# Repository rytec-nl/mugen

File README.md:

# Mugen, my implementation

This project is born because I wanted to connect an external amplifier to my Samsung smart tv that fits my tv cabinet.
The obvious step was to build a hybrid tube/transistor amplifier myself. I was pointed to the Mugen hybrid amplifier. It fit my size and power requirements (I have 2 60W Visaton speakers). Altough there were some things that need to be added for it to work with my setup. 

For one i want to use my tv remote to change the volume, so I will need to implement a IR reciever that controls a variable resistor in the input signal. This means an additional power supply, a microcontroller to process the IR signals and control a digital potentiometer. 

The next challenge is that my TV only has an optical audio out, so I need to hook up a optical to aux convertor. My plan as of now is to buy the smallest I can find and build it into the amplifier. If this proves impossible, it will stay as an external box. 

Finally I want the amplifier to look good. So I am planning to change the design to have both tubes above eachother when facing the front of the amplifier. I can then place a see through window in front of the Tubes so they can be seen. Then hookup some LEDs to the microcontroller, and place them behind the tubes for some cool effects. Using the Microcontroller I can the dim the LEDs using a PWM signal. This all being carefull not to let the PWM signal interfere with the audio signal.

## Additions

As I'm working on the amplifier the design is improving. Instead of using plain windows in front of the tubes, the idea now is to use LCD displays where the backlight is removed. This gives a transparent view inside the amplifier when nothing is displayed. When needed lights inside the amp. will light up, and whatever is shown on the LCD becomes visible. This will be used for volume indication. 

In order for this to be implemented, in stead of simply adding a power supply to the main power board, a completely extra PCB will be added for the logic needed. 

## Todo

- [ ] Power Supply
   - [x] original schematic
   - [ ] schematic review 
   - [x] PCB
   - [ ] PCB review 
- [ ] Amplifier
   - [x] schematic 
   - [ ] schematic review
   - [ ] PCB
   - [ ] PCB review
- [ ] Logic board
   - [ ] schematic 
   - [ ] schematic review
   - [ ] PCB
   - [ ] PCB review
- [ ] Case
   - [ ] Front
      - [ ] design
      - [ ] build
   - [ ] back
      - [ ] design
      - [ ] build
   - [ ] bottom/top
   - [ ] sides
 - [ ] Firmware
    - [x] IR reciever test
    - [ ] IR reciever
    - [ ] Volume control
    - [ ] LED PWM
    - [ ] LED Level Control
    - [x] LCD control test
    - [ ] LCD control

## KiCad

The PCBs are designed using [KiCad](http://kicad.org/). This is the most usable free PCB design software I could find, that also works on Linux. Before this project I normally would use [Eagle](https://www.autodesk.com/products/eagle/overview), I even started this project using Eagle. But for me it is just to expensive for boards larger than `160mm x 100mm` ($65/month or in my case €85/month). So I chose a free alternative, that so far I am liking very much!

## Power Supply

### Schematic & PCB

### 3D View

## Amplifier

### Schematic & PCB

### 3D View

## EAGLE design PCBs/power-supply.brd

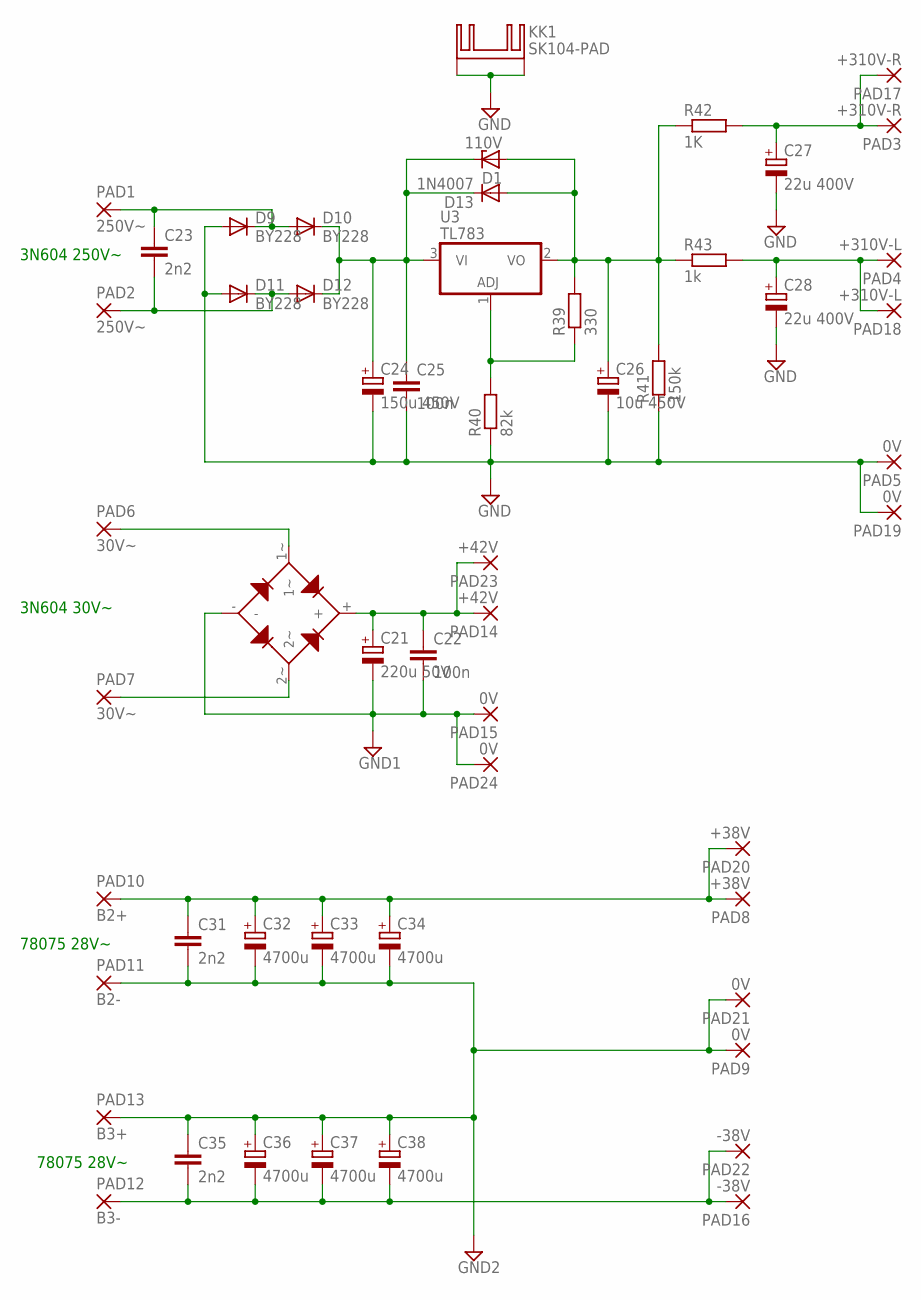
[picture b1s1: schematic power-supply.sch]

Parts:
C21: 220u 50V; E5-10,5
C22: 100n; C050-025X075
C23, C31, C35: 2n2; C225-087X268
C24: 150u 450V; E7,5-18
C25: 100n; C150-054X183
C26: 10u 450V; E7,5-16
C27, C28: 22u 400V; E5-13
C32, C33, C34, C36, C37, C38: 4700u; EB35D
D1: 110V; F126Z10
D9, D10, D11, D12: BY228; SOD64-10
D13: 1N4007; DO41-10
KK1: SK104-PAD
PAD1, PAD2: 250V~; 3,81/1,4
PAD3, PAD17: +310V-R; 3,81/1,4
PAD4, PAD18: +310V-L; 3,81/1,4
PAD5, PAD9, PAD15, PAD19, PAD21, PAD24: 0V; 3,81/1,4
PAD6, PAD7: 30V~; 3,81/1,4
PAD8, PAD20: +38V; 3,81/1,4
PAD10: B2+; 3,81/1,4
PAD11: B2-; 3,81/1,4
PAD12: B3-; 3,81/1,4
PAD13: B3+; 3,81/1,4
PAD14, PAD23: +42V; 3,81/1,4
PAD16, PAD22: -38V; 3,81/1,4
R39: 330; 0207/7
R40: 82k; 0617/22
R41: 150k; 0617/22
R42: 1K; 0309/12
R43: 1k; 0309/12
U3: TL783; TO220V
U$1: W10G; WOG

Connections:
GND: C24.-, C25.2, C26.-, C27.-, C28.-, D9.A, D11.A, KK1.K1, KK1.K2, PAD5.1, PAD19.1, R40.1, R41.1
GND1: C21.-, C22.2, PAD15.1, PAD24.1, U$1.-
GND2: C31.2, C32.-, C33.-, C34.-, C35.1, C36.+, C37.+, C38.+, PAD9.1, PAD11.1, PAD13.1, PAD21.1
unnamed: C23.1, D9.C, D10.A, PAD1.1
unnamed: C23.2, D11.C, D12.A, PAD2.1
unnamed: C27.+, PAD3.1, PAD17.1, R42.2
unnamed: C24.+, C25.1, D1.C, D10.C, D12.C, D13.C, U3.3 (VI)
unnamed: R39.1, R40.2, U3.1 (ADJ)
unnamed: C26.+, D1.A, D13.A, R39.2, R41.2, R42.1, R43.1, U3.2 (VO)
unnamed: C28.+, PAD4.1, PAD18.1, R43.2
unnamed: PAD6.1, U$1.1~
unnamed: PAD7.1, U$1.2~
unnamed: C31.1, C32.+, C33.+, C34.+, PAD8.1, PAD10.1, PAD20.1
unnamed: C35.2, C36.-, C37.-, C38.-, PAD12.1, PAD16.1, PAD22.1
unnamed: C21.+, C22.1, PAD14.1, PAD23.1, U$1.+

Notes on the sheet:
3N604 250V~
3N604 30V~
78075 28V~

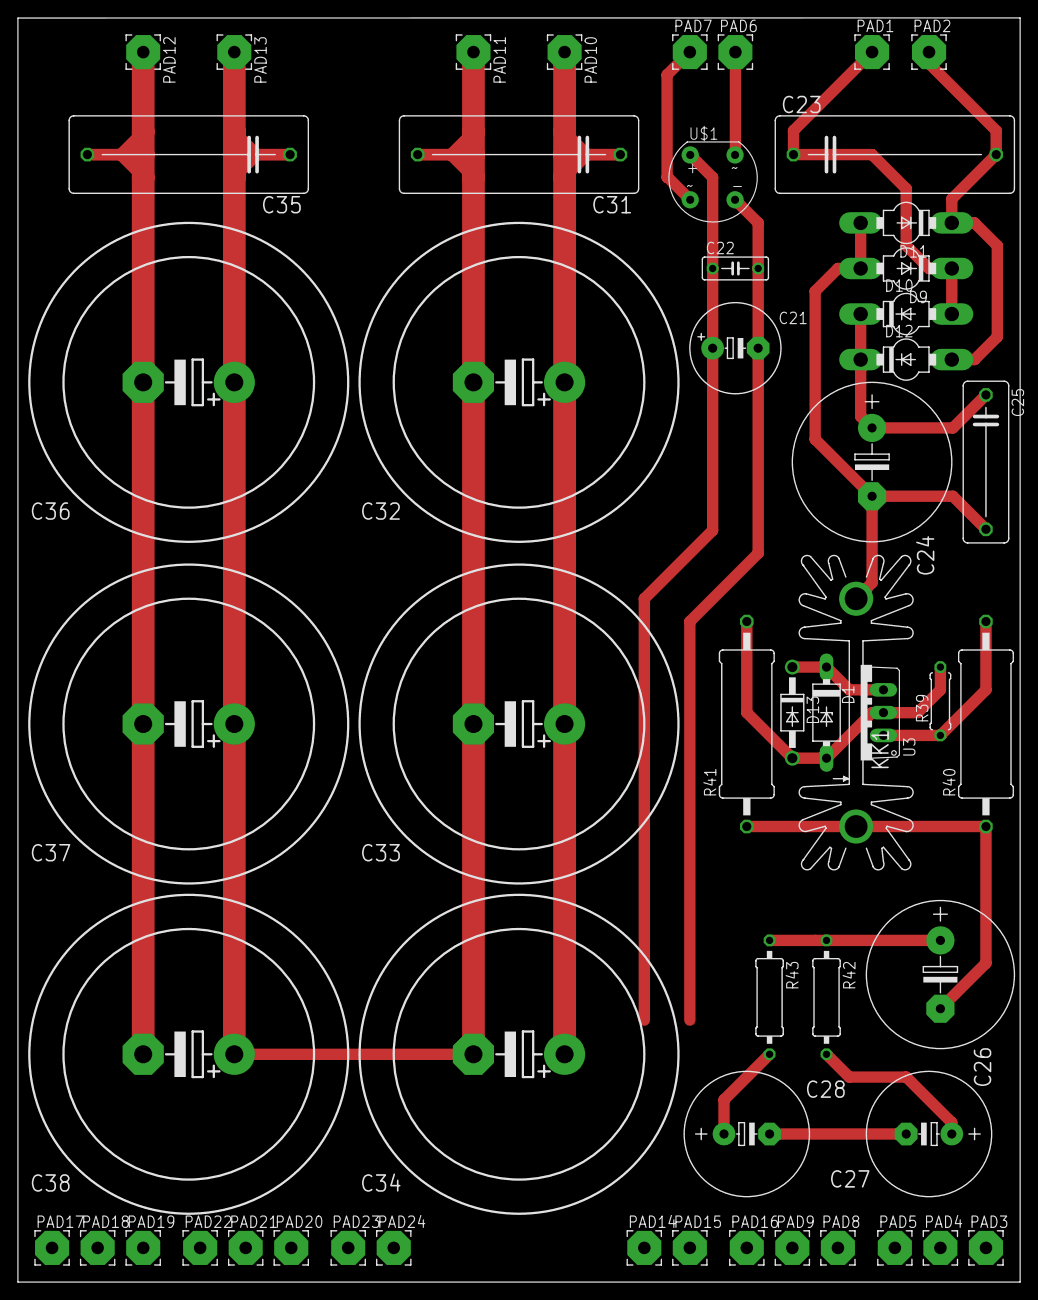
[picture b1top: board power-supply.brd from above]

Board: 2 copper layers, 111.8 x 141.0 mm, 54 parts (0 on the bottom side), 15 nets.

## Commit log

2018-03-23 Initial commit.
2018-03-23 Added readme.
2018-03-23 added some structure.
2018-03-24 Started amp.
2018-03-24 Updated README.
2018-03-24 Basic design done.
2018-03-24 Added power supply image.
2018-03-27 Created kicad project.
2018-03-27 Started on power supply in kicad.
2018-03-28 First kicad version of power supply .
2018-03-29 Small change.
2018-04-02 Started on amplifier pcb .
2018-04-02 Added image.
2018-04-05 updated to kicad 5.
2018-04-06 Changed footprints to kicad 5 names.
2018-04-06 Updated 3D image with ray-tracing.
2018-04-13 fixed schematic.
2018-04-13 Raw finish of amp. schematic.
2018-04-13 Crude start of pcb.
2018-04-15 Fixed power-supply schematic.
2018-04-15 Added correct annotation and started assigning footprints.
2018-04-15 Updated PCB image.
2018-04-16 Updated amp. sch. image.
2018-04-17 amp. sch. done, all footprints added.
2018-04-19 Rough component placement amp. pcb.
2021-11-08 Update README.md
    https://forum.kicad.info/t/warning-avoid-all-links-to-kicad-pcb-org-use-kicad-org/31521
